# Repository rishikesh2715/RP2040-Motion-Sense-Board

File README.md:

# AN updated version of this board is available [here](https://github.com/rishikesh2715/RP2040_Motion_Logger)

# RP2040-Motion-Sense-Board

A microcontroller PCB based on the RP2040 MCU from Raspberry Pi with an on-board high-performance IMU, 2S LiPo battery charging circuit, 32 MB quad SPI flash memory, and a bunch of GPIO breakouts.

## Features

- ICM 42688-P IMU
- 2S LiPo battery charging circuit
- 32 MB quad SPI flash memory
- TC2030 debug port
- USB C
- ESD protection circuit
- RGB LED
- Multilple GPIO breakouts
- 1 I2C
- 4 ADC
- 1 UART

## Disclaimer

I have not personally tested this board. If you want to manufacture it, you should carefully go through the design once. Downloading this project and opening it in KiCad and running the ERC or DRC will result in many warnings, but almost all of them are safe to ignore as most of them are courtyard overlapping warnings.

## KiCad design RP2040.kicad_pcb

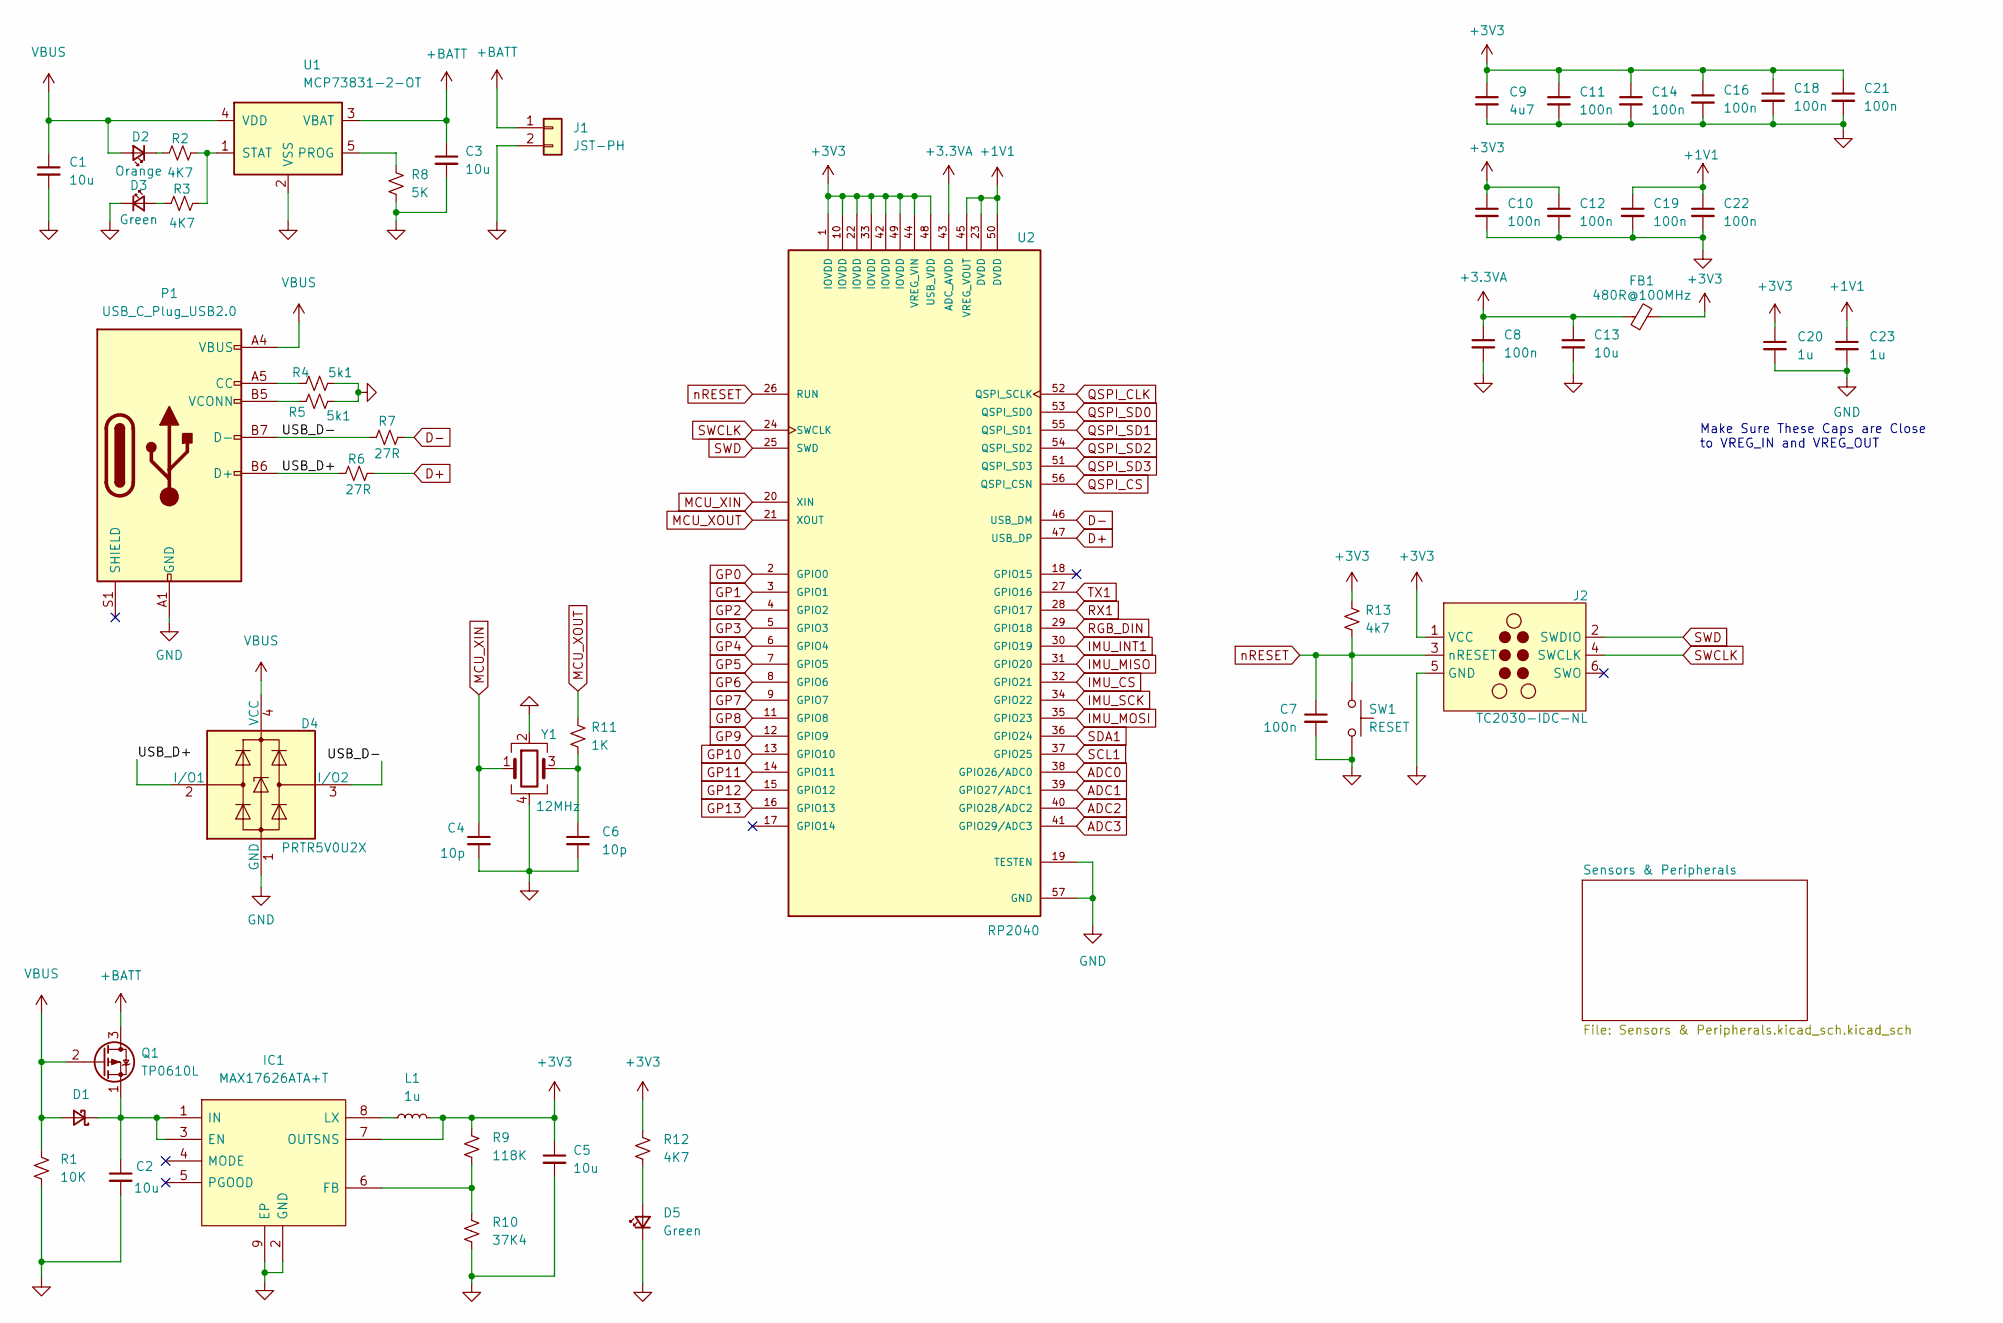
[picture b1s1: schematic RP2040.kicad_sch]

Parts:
C1, C2, C3, C5: 10u; C_0805_2012Metric
C4, C6: 10p; C_0402_1005Metric
C7, C8, C10, C11, C12, C14, C16, C18, C19, C21, C22: 100n; C_0402_1005Metric
C9: 4u7; C_0402_1005Metric
C13: 10u; C_0402_1005Metric
C20, C23: 1u; C_0402_1005Metric
D1: D_Schottky_Small; D_1206_3216Metric
D2: Orange; LED_0603_1608Metric
D3, D5: Green; LED_0603_1608Metric
D4: PRTR5V0U2X; SOT-143
FB1: 480R@100MHz; R_0402_1005Metric
IC1: MAX17626ATA+T; Mouser Part Number 700-MAX17626ATA+T
J1: JST-PH; JST_PH_S2B-PH-SM4-TB_1x02-1MP_P2.00mm_Horizontal
J2: TC2030-IDC-NL; Tag-Connect_TC2030-IDC-NL_2x03_P1.27mm_Vertical
L1: 1u; L_1008_2520Metric
P1: USB_C_Plug_USB2.0; USB_C_Receptacle_HRO_TYPE-C-31-M-12
Q1: TP0610L; TSOT-23
R1: 10K; R_0603_1608Metric
R2, R3, R12: 4K7; R_0402_1005Metric
R4, R5: 5k1; R_0402_1005Metric
R6, R7: 27R; R_0402_1005Metric
R8: 5K; R_0402_1005Metric
R9: 118K; R_0603_1608Metric
R10: 37K4; R_0603_1608Metric
R11: 1K; R_0402_1005Metric
R13: 4k7; R_0402_1005Metric
SW1: RESET; SW_SPST_B3U-1000P
U1: MCP73831-2-OT; SOT-23-5
U2: RP2040; QFN40P700X700X90-57N; PARTREV 1.6.1
Y1: 12MHz; Crystal_SMD_3225-4Pin_3.2x2.5mm

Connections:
+1V1: C19.1, C22.1, C23.1, U2.23 (DVDD), U2.45 (VREG_VOUT), U2.50 (DVDD)
+3.3VA: C8.1, C13.1, FB1.1, U2.43 (ADC_AVDD)
+3V3: C5.1, C9.1, C10.1, C11.1, C12.1, C14.1, C16.1, C18.1, C20.1, C21.1, FB1.2, IC1.7 (OUTSNS), J2.1 (VCC), L1.2, R9.1, R12.1, R13.1, U2.1 (IOVDD), U2.10 (IOVDD), U2.22 (IOVDD), U2.33 (IOVDD), U2.42 (IOVDD), U2.44 (VREG_VIN), U2.48 (USB_VDD), U2.49 (IOVDD); also elsewhere on the board
+BATT: C3.1, J1.1, Q1.3 (D), U1.3 (VBAT)
/USB_D+: D4.2 (I/O1), P1.B6 (D+), R6.1
/USB_D-: D4.3 (I/O2), P1.B7 (D-), R7.1
ADC0: U2.38 (GPIO26/ADC0); also elsewhere on the board
ADC1: U2.39 (GPIO27/ADC1); also elsewhere on the board
ADC2: U2.40 (GPIO28/ADC2); also elsewhere on the board
ADC3: U2.41 (GPIO29/ADC3); also elsewhere on the board
D+: R6.2, U2.47 (USB_DP)
D-: R7.2, U2.46 (USB_DM)
GND: C1.2, C2.2, C3.2, C4.2, C5.2, C6.2, C7.2, C8.2, C9.2, C10.2, C11.2, C12.2, C13.2, C14.2, C16.2, C18.2, C19.2, C20.2, C21.2, C22.2, C23.2, D3.1 (K), D4.1 (GND), D5.1 (K), IC1.2 (GND), IC1.9 (EP), J1.2, J2.5 (GND), P1.A1 (GND), P1.A12 (GND), P1.B1 (GND), P1.B12 (GND), R1.2, R4.2, R5.2, R8.2, R10.2, SW1.2, U1.2 (VSS), U2.19 (TESTEN), U2.57 (GND), Y1.2, Y1.4; also elsewhere on the board
GP0: U2.2 (GPIO0); also elsewhere on the board
GP1: U2.3 (GPIO1); also elsewhere on the board
GP2: U2.4 (GPIO2); also elsewhere on the board
GP3: U2.5 (GPIO3); also elsewhere on the board
GP4: U2.6 (GPIO4); also elsewhere on the board
GP5: U2.7 (GPIO5); also elsewhere on the board
GP6: U2.8 (GPIO6); also elsewhere on the board
GP7: U2.9 (GPIO7); also elsewhere on the board
GP8: U2.11 (GPIO8); also elsewhere on the board
GP9: U2.12 (GPIO9); also elsewhere on the board
GP10: U2.13 (GPIO10); also elsewhere on the board
GP11: U2.14 (GPIO11); also elsewhere on the board
GP12: U2.15 (GPIO12); also elsewhere on the board
GP13: U2.16 (GPIO13); also elsewhere on the board
IMU_CS: U2.32 (GPIO21); also elsewhere on the board
IMU_INT1: U2.30 (GPIO19); also elsewhere on the board
IMU_MISO: U2.31 (GPIO20); also elsewhere on the board
IMU_MOSI: U2.35 (GPIO23); also elsewhere on the board
IMU_SCK: U2.34 (GPIO22); also elsewhere on the board
MCU_XIN: C4.1, U2.20 (XIN), Y1.1
MCU_XOUT: R11.1, U2.21 (XOUT)
unnamed: C2.1, D1.1 (K), IC1.1 (IN), IC1.3 (EN), Q1.1 (S)
unnamed: C6.1, R11.2, Y1.3
unnamed: D2.1 (K), R2.1
unnamed: D3.2 (A), R3.1
unnamed: D5.2 (A), R12.2
unnamed: IC1.6 (FB), R9.2, R10.1
unnamed: IC1.8 (LX), L1.1
unnamed: P1.A5 (CC), R4.1
unnamed: P1.B5 (VCONN), R5.1
unnamed: R2.2, R3.2, U1.1 (STAT)
unnamed: R8.1, U1.5 (PROG)
QSPI_CLK: U2.52 (QSPI_SCLK); also elsewhere on the board
QSPI_CS: U2.56 (QSPI_CSN); also elsewhere on the board
QSPI_SD0: U2.53 (QSPI_SD0); also elsewhere on the board
QSPI_SD1: U2.55 (QSPI_SD1); also elsewhere on the board
QSPI_SD2: U2.54 (QSPI_SD2); also elsewhere on the board
QSPI_SD3: U2.51 (QSPI_SD3); also elsewhere on the board
RGB_DIN: U2.29 (GPIO18); also elsewhere on the board
RX1: U2.28 (GPIO17); also elsewhere on the board
SCL1: U2.37 (GPIO25); also elsewhere on the board
SDA1: U2.36 (GPIO24); also elsewhere on the board
SWCLK: J2.4 (SWCLK), U2.24 (SWCLK)
SWD: J2.2 (SWDIO), U2.25 (SWD)
TX1: U2.27 (GPIO16); also elsewhere on the board
VBUS: C1.1, D1.2 (A), D2.2 (A), D4.4 (VCC), P1.A4 (VBUS), P1.A9 (VBUS), P1.B4 (VBUS), P1.B9 (VBUS), Q1.2 (G), R1.1, U1.4 (VDD); also elsewhere on the board
nRESET: C7.1, J2.3 (nRESET), R13.2, SW1.1, U2.26 (RUN)

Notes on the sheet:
Make Sure These Caps are Close to VREG_IN and VREG_OUT

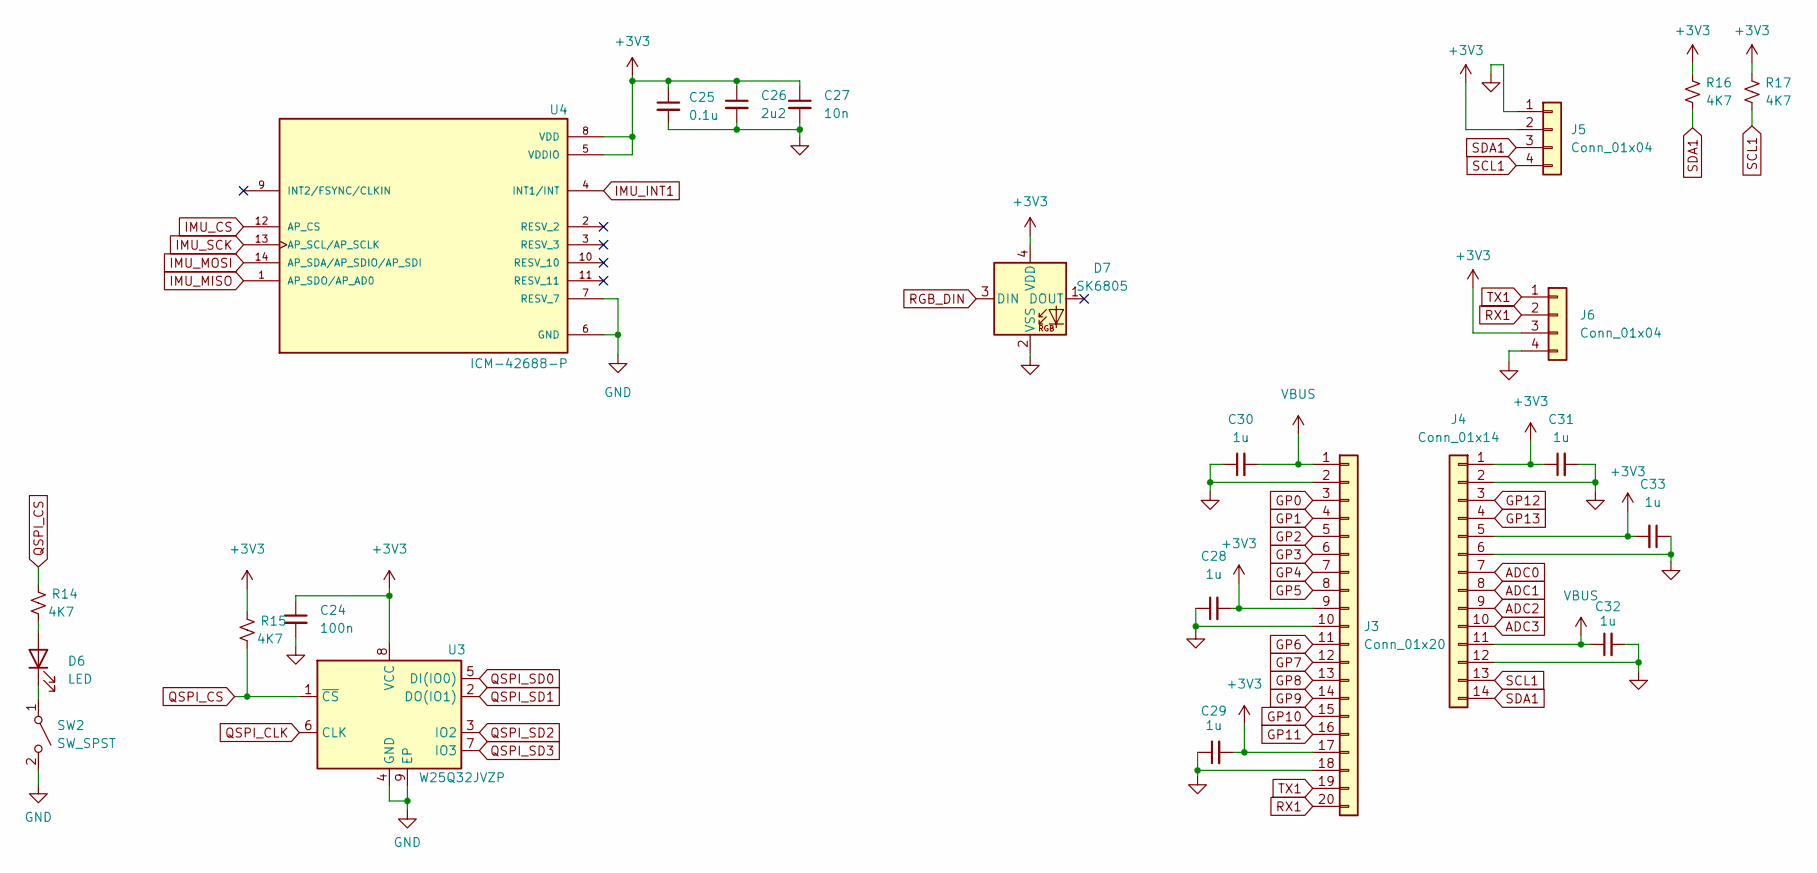
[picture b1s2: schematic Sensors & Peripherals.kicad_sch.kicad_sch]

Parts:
C24: 100n; C_0402_1005Metric
C25: 0.1u; C_0402_1005Metric
C26: 2u2; C_0603_1608Metric
C27: 10n; C_0402_1005Metric
C28, C29, C30, C31, C32, C33: 1u; C_0402_1005Metric
D6: LED; LED_0603_1608Metric
D7: SK6805; LED_SK6805_PLCC4_2.4x2.7mm_P1.3mm
J3: Conn_01x20; PinSocket_1x20_P2.54mm_Vertical
J4: Conn_01x14; PinHeader_1x14_P2.54mm_Vertical
J5, J6: Conn_01x04; JST_SH_SM04B-SRSS-TB_1x04-1MP_P1.00mm_Horizontal
R14, R15, R16, R17: 4K7; R_0402_1005Metric
SW2: SW_SPST; SW_SPST_B3U-1000P
U3: W25Q32JVZP; W25Q64JVXGIQ_TR
U4: ICM-42688-P; ICP-42688-P; PARTREV 1.2

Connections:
+3V3: C24.1, C25.1, C26.1, C27.1, C28.2, C29.2, C31.1, C33.2, D7.4 (VDD), J3.9, J3.17, J4.1, J4.5, J5.2, J6.3, R15.1, R16.1, R17.1, U3.8 (VCC), U4.5 (VDDIO), U4.8 (VDD); also elsewhere on the board
ADC0: J4.7; also elsewhere on the board
ADC1: J4.8; also elsewhere on the board
ADC2: J4.9; also elsewhere on the board
ADC3: J4.10; also elsewhere on the board
GND: C24.2, C25.2, C26.2, C27.2, C28.1, C29.1, C30.1, C31.2, C32.2, C33.1, D7.2 (VSS), J3.2, J3.10, J3.18, J4.2, J4.6, J4.12, J5.1, J6.4, SW2.2 (B), U3.4 (GND), U3.9 (EP), U4.6 (GND), U4.7 (RESV_7); also elsewhere on the board
GP0: J3.3; also elsewhere on the board
GP1: J3.4; also elsewhere on the board
GP2: J3.5; also elsewhere on the board
GP3: J3.6; also elsewhere on the board
GP4: J3.7; also elsewhere on the board
GP5: J3.8; also elsewhere on the board
GP6: J3.11; also elsewhere on the board
GP7: J3.12; also elsewhere on the board
GP8: J3.13; also elsewhere on the board
GP9: J3.14; also elsewhere on the board
GP10: J3.15; also elsewhere on the board
GP11: J3.16; also elsewhere on the board
GP12: J4.3; also elsewhere on the board
GP13: J4.4; also elsewhere on the board
IMU_CS: U4.12 (AP_CS); also elsewhere on the board
IMU_INT1: U4.4 (INT1/INT); also elsewhere on the board
IMU_MISO: U4.1 (AP_SDO/AP_AD0); also elsewhere on the board
IMU_MOSI: U4.14 (AP_SDA/AP_SDIO/AP_SDI); also elsewhere on the board
IMU_SCK: U4.13 (AP_SCL/AP_SCLK); also elsewhere on the board
unnamed: D6.1 (K), SW2.1 (A)
unnamed: D6.2 (A), R14.2
QSPI_CLK: U3.6 (CLK); also elsewhere on the board
QSPI_CS: R14.1, R15.2, U3.1 (~CS); also elsewhere on the board
QSPI_SD0: U3.5 (DI(IO0)); also elsewhere on the board
QSPI_SD1: U3.2 (DO(IO1)); also elsewhere on the board
QSPI_SD2: U3.3 (IO2); also elsewhere on the board
QSPI_SD3: U3.7 (IO3); also elsewhere on the board
RGB_DIN: D7.3 (DIN); also elsewhere on the board
RX1: J3.20, J6.2; also elsewhere on the board
SCL1: J4.13, J5.4, R17.2; also elsewhere on the board
SDA1: J4.14, J5.3, R16.2; also elsewhere on the board
TX1: J3.19, J6.1; also elsewhere on the board
VBUS: C30.2, C32.1, J3.1, J4.11; also elsewhere on the board

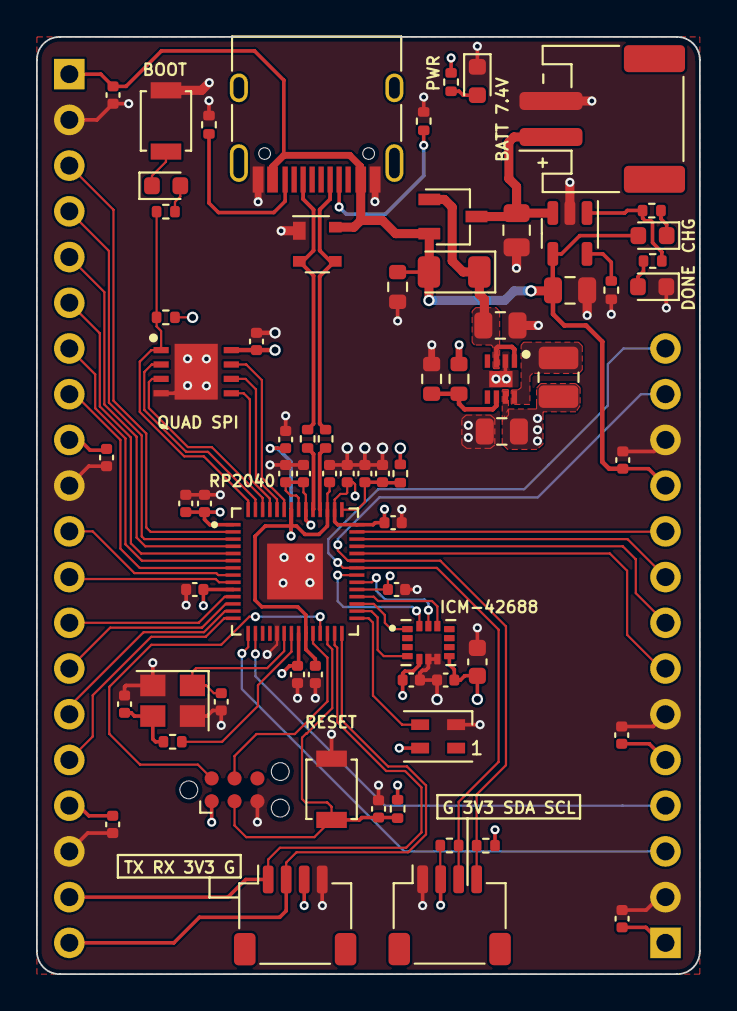
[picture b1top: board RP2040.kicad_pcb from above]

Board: 4 copper layers, 36.8 x 52.1 mm, 73 parts (0 on the bottom side), 62 nets.

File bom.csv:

Designator,Footprint,Quantity,Value,LCSC Part #
SW2,SW_SPST_B3U-1000P,1,SW_SPST,
Y1,Crystal_SMD_3225-4Pin_3.2x2.5mm,1,12MHz,
J3,PinSocket_1x20_P2.54mm_Vertical,1,Conn_01x20,
D1,D_1206_3216Metric,1,D_Schottky_Small,
C22,C_0402_1005Metric,1,100n,
C18,C_0402_1005Metric,1,100n,
C30,C_0402_1005Metric,1,1u,
C8,C_0402_1005Metric,1,100n,
C29,C_0402_1005Metric,1,1u,
J1,JST_PH_S2B-PH-SM4-TB_1x02-1MP_P2.00mm_Horizontal,1,JST-PH,
C24,C_0402_1005Metric,1,100n,
C27,C_0402_1005Metric,1,10n,
D5,LED_0603_1608Metric,1,Green,
Q1,TSOT-23,1,TP0610L,
U4,ICP-42688-P,1,ICM-42688-P,
C33,C_0402_1005Metric,1,1u,
C6,C_0402_1005Metric,1,10p,
R10,R_0603_1608Metric,1,37K4,
U3,W25Q64JVXGIQ_TR,1,W25Q32JVZP,
R13,R_0402_1005Metric,1,4k7,
R6,R_0402_1005Metric,1,27R,
R5,R_0402_1005Metric,1,5k1,
C11,C_0402_1005Metric,1,100n,
R12,R_0402_1005Metric,1,4K7,
C19,C_0402_1005Metric,1,100n,
J4,PinHeader_1x14_P2.54mm_Vertical,1,Conn_01x14,
R3,R_0402_1005Metric,1,4K7,
C7,C_0402_1005Metric,1,100n,
C32,C_0402_1005Metric,1,1u,
FB1,R_0402_1005Metric,1,480R@100MHz,
D7,LED_SK6805_PLCC4_2.4x2.7mm_P1.3mm,1,SK6805,
R9,R_0603_1608Metric,1,118K,
R15,R_0402_1005Metric,1,4K7,
C9,C_0402_1005Metric,1,4u7,
C21,C_0402_1005Metric,1,100n,
C14,C_0402_1005Metric,1,100n,
R4,R_0402_1005Metric,1,5k1,
C28,C_0402_1005Metric,1,1u,
D4,SOT-143,1,PRTR5V0U2X,
C10,C_0402_1005Metric,1,100n,
R1,R_0603_1608Metric,1,10K,
R7,R_0402_1005Metric,1,27R,
R16,R_0402_1005Metric,1,4K7,
R11,R_0402_1005Metric,1,1K,
C3,C_0805_2012Metric,1,10u,
C2,C_0805_2012Metric,1,10u,
C1,C_0805_2012Metric,1,10u,
R8,R_0402_1005Metric,1,5K,
U2,QFN40P700X700X90-57N,1,RP2040,
D3,LED_0603_1608Metric,1,Green,
C23,C_0402_1005Metric,1,1u,
C4,C_0402_1005Metric,1,10p,
C12,C_0402_1005Metric,1,100n,
D6,LED_0603_1608Metric,1,LED,
C16,C_0402_1005Metric,1,100n,
C20,C_0402_1005Metric,1,1u,
J5,JST_SH_SM04B-SRSS-TB_1x04-1MP_P1.00mm_Horizontal,1,Conn_01x04,
J6,JST_SH_SM04B-SRSS-TB_1x04-1MP_P1.00mm_Horizontal,1,Conn_01x04,
D2,LED_0603_1608Metric,1,Orange,
C31,C_0402_1005Metric,1,1u,
IC1,MAX17626ATA+T,1,MAX17626ATA+T,
C25,C_0402_1005Metric,1,0.1u,
P1,USB_C_Receptacle_HRO_TYPE-C-31-M-12,1,USB_C_Plug_USB2.0,
C26,C_0603_1608Metric,1,2u2,
SW1,SW_SPST_B3U-1000P,1,RESET,
R2,R_0402_1005Metric,1,4K7,
C5,C_0805_2012Metric,1,10u,
J2,Tag-Connect_TC2030-IDC-NL_2x03_P1.27mm_Vertical,1,TC2030-IDC-NL,
R17,R_0402_1005Metric,1,4K7,
R14,R_0402_1005Metric,1,4K7,
U1,SOT-23-5,1,MCP73831-2-OT,
C13,C_0402_1005Metric,1,10u,
L1,L_1008_2520Metric,1,1u,

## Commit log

2024-08-03 Deleted production files from root directory
2024-08-03 updated Production files -- matches JLCPCB format
2024-08-03 updated design files
2024-08-03 updated README file
